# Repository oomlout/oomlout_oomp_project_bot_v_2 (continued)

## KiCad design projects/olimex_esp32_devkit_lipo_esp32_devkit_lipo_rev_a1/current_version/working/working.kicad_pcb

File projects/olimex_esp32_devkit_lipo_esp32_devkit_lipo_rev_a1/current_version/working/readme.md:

# esp32_devkit_lipo
 
## summary 
* id: olimex_esp32_devkit_lipo_esp32_devkit_lipo_rev_a1
* user: olimex
* name: esp32_devkit_lipo
* board: esp32_devkit_lipo_rev_a1
* repo: https://github.com/OLIMEX/ESP32-DevKit-LiPo
* src_file_repo_kicad_pcb: HARDWARE/ESP32-DevKit-LiPo-Rev.A1/ESP32-DevKit-Lipo_Rev_A1.kicad_pcb
* src_file_repo_kicad_pcb_link: https://github.com/OLIMEX/ESP32-DevKit-LiPo/tree/master/HARDWARE/ESP32-DevKit-LiPo-Rev.A1/ESP32-DevKit-Lipo_Rev_A1.kicad_pcb

* src_file_repo_sch: HARDWARE/ESP32-DevKit-LiPo-Rev.A1/ESP32-DevKit-Lipo_Rev_A1.sch
* src_file_repo_sch_link: https://github.com/OLIMEX/ESP32-DevKit-LiPo/tree/master/HARDWARE/ESP32-DevKit-LiPo-Rev.A1/ESP32-DevKit-Lipo_Rev_A1.sch
* full details link: https://github.com/oomlout/oomlout_oomp_project_bot_v_2/tree/main/projects/olimex_esp32_devkit_lipo_esp32_devkit_lipo_rev_a1/current_version/working

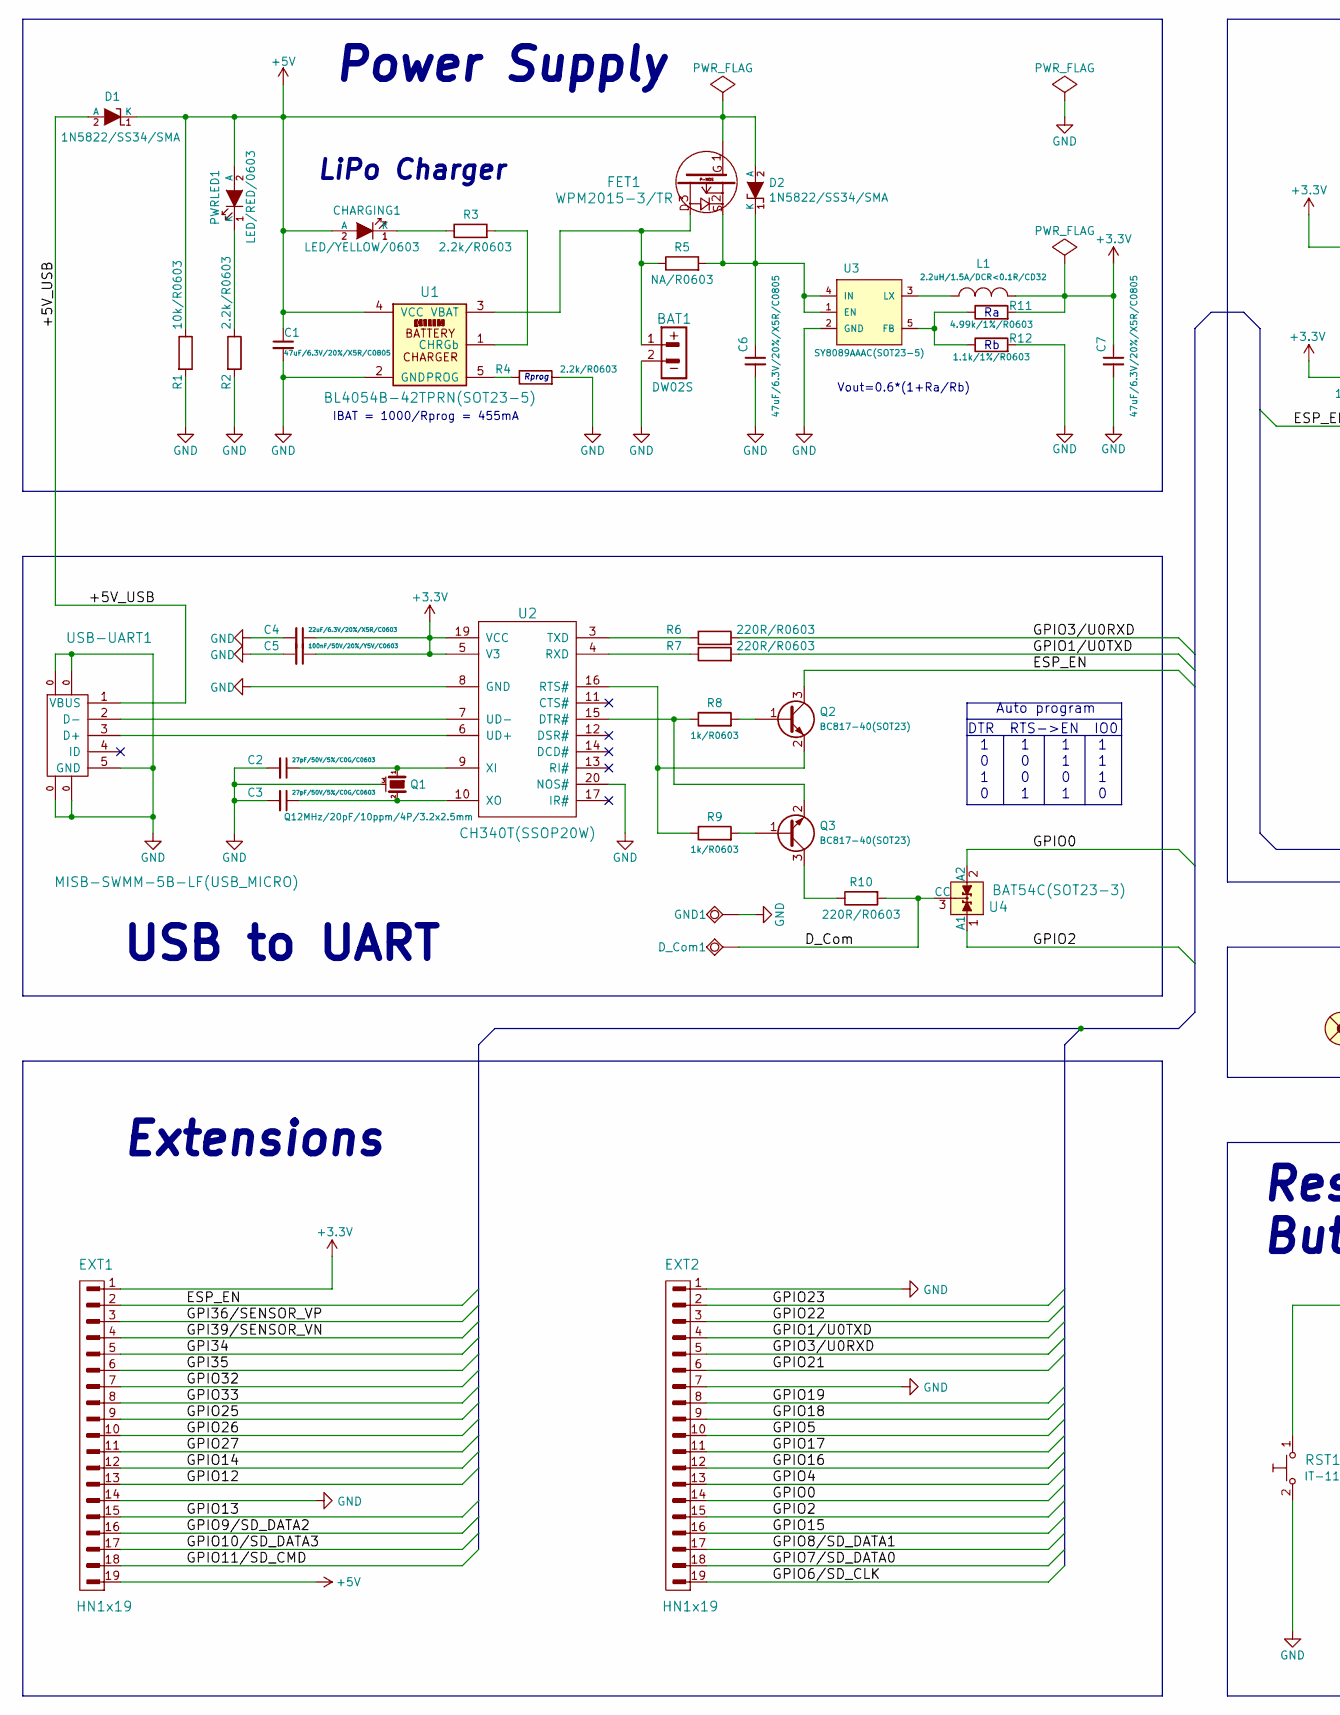
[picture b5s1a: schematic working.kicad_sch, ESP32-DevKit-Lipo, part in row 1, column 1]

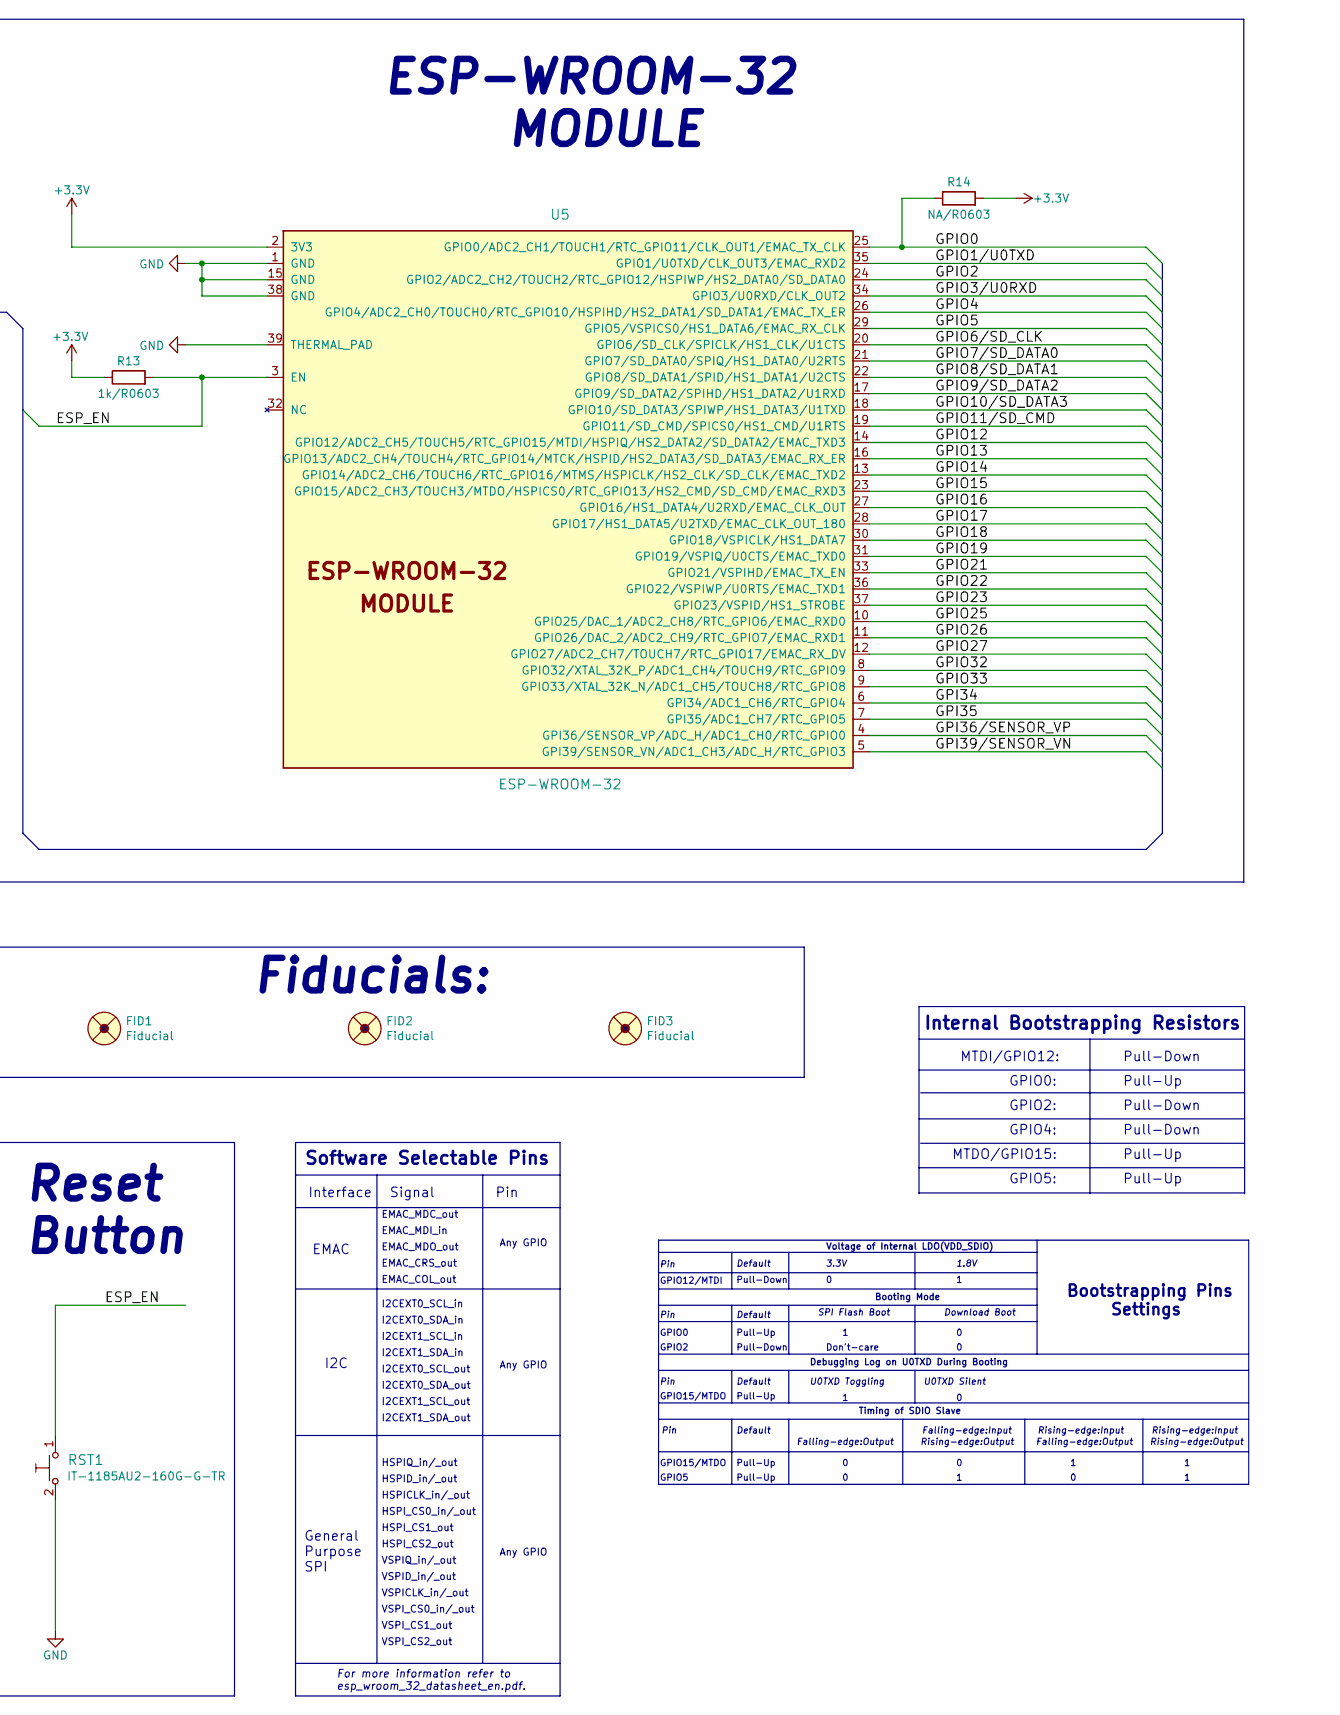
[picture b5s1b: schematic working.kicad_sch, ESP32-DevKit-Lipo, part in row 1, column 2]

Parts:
BAT1: DW02S; LIPO_BAT-CON2DW02R
C1, C6, C7: 47uF/6.3V/20%/X5R/C0805; C_0805_5MIL_DWS
C2, C3: 27pF/50V/5%/C0G/C0603; C_0603_5MIL_DWS
C4: 22uF/6.3V/20%/X5R/C0603; C_0603_5MIL_DWS
C5: 100nF/50V/20%/Y5V/C0603; C_0603_5MIL_DWS
CHARGING1: LED/YELLOW/0603; LED_0603_KA
D1, D2: 1N5822/SS34/SMA; SMA-KA
D_Com1: TESTPAD; TESTPAD_40-ROUND
EXT1, EXT2: HN1x19
FET1: WPM2015-3/TR; SOT23
FID1, FID2, FID3: Fiducial; Fiducial1x3
GND1: TESTPAD; TESTPAD_40-ROUND
L1: 2.2uH/1.5A/DCR<0.1R/CD32; CD32
PWRLED1: LED/RED/0603; LED_0603_KA
Q1: Q12MHz/20pF/10ppm/4P/3.2x2.5mm; TSX-3.2x2.5mm_GND(3)
Q2, Q3: BC817-40(SOT23); SOT23
R1: 10k/R0603; R_0603_5MIL_DWS
R2, R3, R4: 2.2k/R0603; R_0603_5MIL_DWS
R5, R14: NA/R0603; R_0603_5MIL_DWS
R6, R7, R10: 220R/R0603; R_0603_5MIL_DWS
R8, R9, R13: 1k/R0603; R_0603_5MIL_DWS
R11: 4.99k/1%/R0603; R_0603_5MIL_DWS
R12: 1.1k/1%/R0603; R_0603_5MIL_DWS
RST1: IT-1185AU2-160G-G-TR; IT1185AU2_V2
U1: BL4054B-42TPRN(SOT23-5); SOT-23-5
U2: CH340T(SSOP20W); SSOP-20W
U3: SY8089AAAC(SOT23-5); SOT-23-5
U4: BAT54C(SOT23-3); SOT23-3
U5: ESP-WROOM-32; ESP-WROOM-32_MODULE
USB-UART1: MISB-SWMM-5B-LF(USB_MICRO); USB-MICRO_MISB-SWMM-5B_LF

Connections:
+3V3: C4.1, C5.1, C7.1, EXT1.1, L1.2, R11.2, R13.1, R14.2, U2.5 (V3), U2.19 (VCC), U5.2 (3V3)
+5V: C1.1, CHARGING1.2 (A), D1.1 (K), D2.2 (A), EXT1.19, FET1.1, PWRLED1.2 (A), R1.1, U1.4 (VCC)
/+5V_USB: D1.2 (A), USB-UART1.1 (VBUS)
/D_Com: D_Com1.1, R10.2, U4.3 (CC)
/ESP_EN: EXT1.2, Q2.3 (C), R13.2, RST1.1, U5.3 (EN)
/GPI34: EXT1.5, U5.6 (GPI34/ADC1_CH6/RTC_GPIO4)
/GPI35: EXT1.6, U5.7 (GPI35/ADC1_CH7/RTC_GPIO5)
/GPI36/SENSOR_VP: EXT1.3, U5.4 (GPI36/SENSOR_VP/ADC_H/ADC1_CH0/RTC_GPIO0)
/GPI39/SENSOR_VN: EXT1.4, U5.5 (GPI39/SENSOR_VN/ADC1_CH3/ADC_H/RTC_GPIO3)
/GPIO0: EXT2.14, R14.1, U4.2 (A2), U5.25 (GPIO0/ADC2_CH1/TOUCH1/RTC_GPIO11/CLK_OU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)
/GPIO1/U0TXD: EXT2.4, R7.2, U5.35 (GPIO1/U0TXD/CLK_OUT3/EMAC_RXD2)
/GPIO2: EXT2.15, U4.1 (A1), U5.24 (GPIO2/ADC2_CH2/TOUCH2/RTC_GPIO12/HSPIWP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)
/GPIO3/U0RXD: EXT2.5, R6.2, U5.34 (GPIO3/U0RXD/CLK_OUT2)
/GPIO4: EXT2.13, U5.26 (GPIO4/ADC2_CH0/TOUCH0/RTC_GPIO10/HSPIHD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)
/GPIO5: EXT2.10, U5.29 (GPIO5/VSPICS0/HS1_DATA6/EMAC_RX_CLK)
/GPIO6/SD_CLK: EXT2.19, U5.20 (GPIO6/SD_CLK/SPICLK/HS1_CLK/U1CTS)
/GPIO7/SD_DATA0: EXT2.18, U5.21 (GPIO7/SD_DATA0/SPIQ/HS1_DATA0/U2RTS)
/GPIO8/SD_DATA1: EXT2.17, U5.22 (GPIO8/SD_DATA1/SPID/HS1_DATA1/U2CTS)
/GPIO9/SD_DATA2: EXT1.16, U5.17 (GPIO9/SD_DATA2/SPIHD/HS1_DATA2/U1RXD)
/GPIO10/SD_DATA3: EXT1.17, U5.18 (GPIO10/SD_DATA3/SPIWP/HS1_DATA3/U1TXD)
/GPIO11/SD_CMD: EXT1.18, U5.19 (GPIO11/SD_CMD/SPICS0/HS1_CMD/U1RTS)
/GPIO12: EXT1.13, U5.14 (GPIO12/ADC2_CH5/TOUCH5/RTC_GPIO15/MTDI/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)
/GPIO13: EXT1.15, U5.16 (GPIO13/ADC2_CH4/TOUCH4/RTC_GPIO14/MTCK/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)
/GPIO14: EXT1.12, U5.13 (GPIO14/ADC2_CH6/TOUCH6/RTC_GPIO16/MTMS/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)
/GPIO15: EXT2.16, U5.23 (GPIO15/ADC2_CH3/TOUCH3/MTDO/HSPICS0/RTC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)
/GPIO16: EXT2.12, U5.27 (GPIO16/HS1_DATA4/U2RXD/EMAC_CLK_OUT)
/GPIO17: EXT2.11, U5.28 (GPIO17/HS1_DATA5/U2TXD/EMAC_CLK_OUT_180)
/GPIO18: EXT2.9, U5.30 (GPIO18/VSPICLK/HS1_DATA7)
/GPIO19: EXT2.8, U5.31 (GPIO19/VSPIQ/U0CTS/EMAC_TXD0)
/GPIO21: EXT2.6, U5.33 (GPIO21/VSPIHD/EMAC_TX_EN)
/GPIO22: EXT2.3, U5.36 (GPIO22/VSPIWP/U0RTS/EMAC_TXD1)
/GPIO23: EXT2.2, U5.37 (GPIO23/VSPID/HS1_STROBE)
/GPIO25: EXT1.9, U5.10 (GPIO25/DAC_1/ADC2_CH8/RTC_GPIO6/EMAC_RX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)
/GPIO26: EXT1.10, U5.11 (GPIO26/DAC_2/ADC2_CH9/RTC_GPIO7/EMAC_RX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)
/GPIO27: EXT1.11, U5.12 (GPIO27/ADC2_CH7/TOUCH7/RTC_GPIO17/EMAC_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)
/GPIO32: EXT1.7, U5.8 (GPIO32/XTAL_32K_P/ADC1_CH4/TOUCH9/RTC_G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)
/GPIO33: EXT1.8, U5.9 (GPIO33/XTAL_32K_N/ADC1_CH5/TOUCH8/RTC_G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)
GND: BAT1.2, C1.2, C2.2, C3.2, C4.2, C5.2, C6.2, C7.2, EXT1.14, EXT2.1, EXT2.7, GND1.1, Q1.3 (case), R1.2, R2.2, R4.2, R12.2, RST1.2, U1.2 (GND), U2.8 (GND), U2.20 (NOS#), U3.2 (GND), U5.1 (GND), U5.15 (GND), U5.38 (GND), U5.39 (THERMAL_PAD), USB-UART1.0, USB-UART1.5 (GND)
unnamed: BAT1.1, FET1.3, R5.1, U1.3 (VBAT)
unnamed: C2.1, Q1.1, U2.9 (XI)
unnamed: C3.1, Q1.2, U2.10 (XO)
unnamed: C6.1, D2.1 (K), FET1.2, R5.2, U3.1 (EN), U3.4 (IN)
unnamed: CHARGING1.1 (K), R3.1
unnamed: L1.1, U3.3 (LX)
unnamed: PWRLED1.1 (K), R2.1
unnamed: Q2.1 (B), R8.2
unnamed: Q2.2 (E), R9.1, U2.16 (RTS#)
unnamed: Q3.1 (B), R9.2
unnamed: Q3.2 (E), R8.1, U2.15 (DTR#)
unnamed: Q3.3 (C), R10.1
unnamed: R3.2, U1.1 (CHRGb)
unnamed: R4.1, U1.5 (PROG)
unnamed: R6.1, U2.3 (TXD)
unnamed: R7.1, U2.4 (RXD)
unnamed: R11.1, R12.1, U3.5 (FB)
unnamed: U2.6 (UD+), USB-UART1.3 (D+)
unnamed: U2.7 (UD-), USB-UART1.2 (D-)

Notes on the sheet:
Fiducials:
GPIO0
Pin
GPIO0:
VSPI_CS0_in/_out
1.8V
I2CEXT1_SCL_out
Falling-edge:Input
Pull-Up
Interface
EMAC_MDI_in
Timing of SDIO Slave
General Purpose SPI
EMAC_MDC_out
Pull-Down
GPIO15/MTDO
Default
Rising-edge:Output
DTR RTS->EN IO0
VSPICLK_in/_out
U0TXD Silent
I2CEXT0_SCL_out
IBAT = 1000/Rprog = 455mA
Any GPIO
GPIO5
HSPI_CS2_out
Bootstrapping Pins Settings
Vout=0.6*(1+Ra/Rb)
MTDO/GPIO15:
Rprog
GPIO12/MTDI
I2CEXT0_SCL_in
Reset Button
GPIO2:
VSPI_CS2_out
LiPo Charger
HSPI_CS0_in/_out
Falling-edge:Output
EMAC_COL_out
GPIO4:

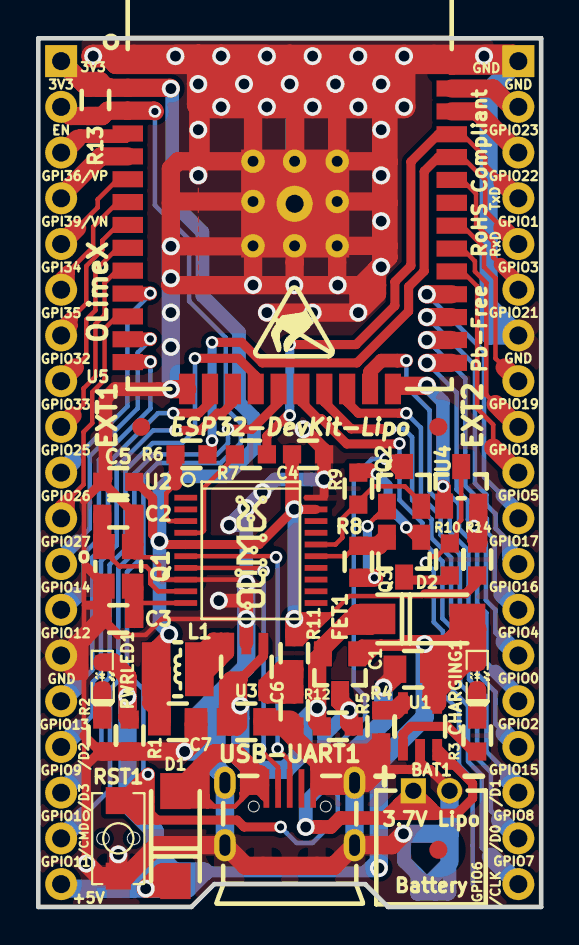
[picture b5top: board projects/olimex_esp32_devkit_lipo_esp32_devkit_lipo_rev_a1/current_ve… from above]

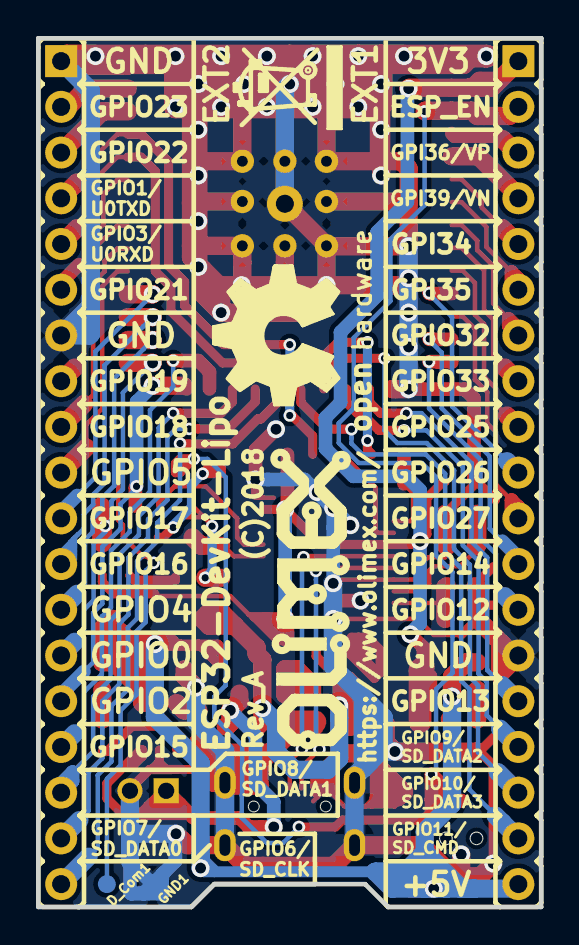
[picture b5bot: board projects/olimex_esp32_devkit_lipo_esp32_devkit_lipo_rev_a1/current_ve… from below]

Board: 2 copper layers, 27.9 x 48.3 mm, 50 parts (7 on the bottom side), 57 nets.

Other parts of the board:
Logo_OSHW: LOGO_OPENHARDWARE_8x8
Olimex_Logo_Big: OLIMEX_LOGO_TB
Olimex_Logo_Small: LOGO_OLIMEX_80
Sign_Antistatic: Val**; LOGO_ANTISTATIC_SMALL_4.5mmX2.8mm
Sign_RecycleBin: LOGO_RECYCLEBIN_1
